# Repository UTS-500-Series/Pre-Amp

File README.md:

# kiCAD Series 500 Compatible Template
Template PCB Series 500 compatible, for kiCAD.
Made by Tormy Van Cool

If this project was useful to you for your porjects and saved you time, please pay me a drink

## Licence

Copyright 2026 the UTS 500 Series team.

This source describes Open Hardware and is licensed under the CERN-OHL-S v2.

You may redistribute and modify this source and make products using it under
the terms of the [CERN-OHL-S v2](https://ohwr.org/cern_ohl_s_v2.txt).

This source is distributed WITHOUT ANY EXPRESS OR IMPLIED WARRANTY, INCLUDING
OF MERCHANTABILITY, SATISFACTORY QUALITY AND FITNESS FOR A PARTICULAR PURPOSE.
Please see the CERN-OHL-S v2 for applicable conditions.

Source location: https://github.com/UTS-500-Series/Pre-Amp

As per CERN-OHL-S v2 section 4, should You produce hardware based on this
source, You must where practicable maintain the Source Location visible on the
external case of the preamp module or other products you make
using this source.

The full licence text is in [LICENSE](LICENSE).

### Third-party material

This licence covers the team's own work. It does not cover, and grants no rights in,
the following:

- **The circuit** is [ESP Project 66](https://sound-au.com/project66.htm) by Rod Elliott,
  with phantom power from [Project 96](https://sound-au.com/project96.htm). ESP's terms
  permit construction for personal use but not commercial manufacture.
- **The board template** (the card outline, edge connector footprint and the text above
  this section) is Tormy Van Cool's kiCAD Series 500 template, published under the GNU GPL
  v3. That material stays under the GPL v3, whose text is kept in
  [LICENSE-GPL-3.0](LICENSE-GPL-3.0).

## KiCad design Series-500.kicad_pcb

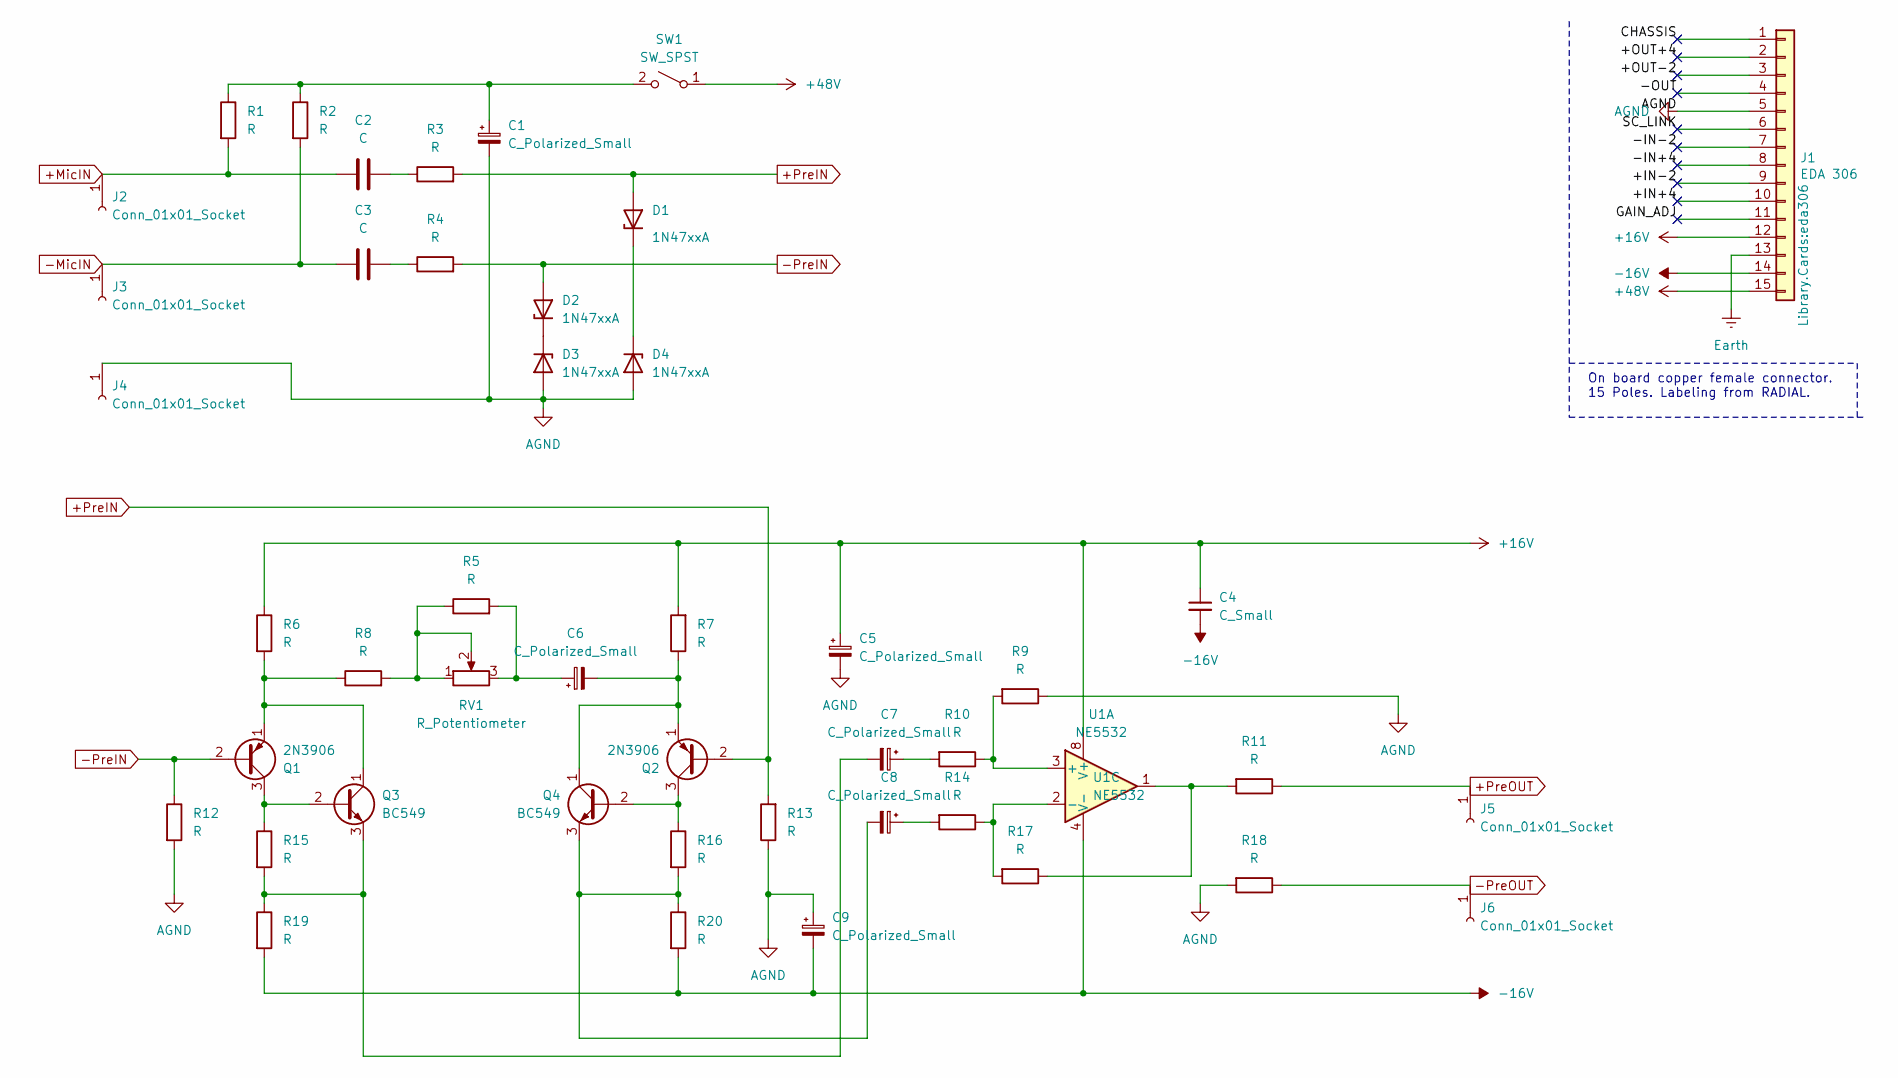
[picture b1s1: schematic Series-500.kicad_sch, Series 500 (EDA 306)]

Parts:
C1: C_Polarized_Small; CP_Radial_D5.0mm_P2.50mm
C2, C3: C; C_Radial_D5.0mm_H5.0mm_P2.00mm
C4: C_Small; C_Disc_D5.0mm_W2.5mm_P5.00mm
C5, C9: C_Polarized_Small; CP_Radial_D8.0mm_P3.80mm
C6: C_Polarized_Small; CP_Radial_D13.0mm_P5.00mm
C7, C8: C_Polarized_Small; CP_Radial_D5.0mm_P2.00mm
D1, D2, D3, D4: 1N47xxA; D_DO-41_SOD81_P10.16mm_Horizontal
J1: EDA 306; eda306
J2, J3, J4, J5, J6: Conn_01x01_Socket; PinHeader_1x01_P2.00mm_Vertical
Q1, Q2: 2N3906; TO-92_Inline
Q3, Q4: BC549; TO-92_Inline
R1, R2, R3, R4, R5, R6, R7, R8, R9, R10, R11, R12, R13, R14, R15, R16, R17, R18, R19, R20: R; R_Axial_DIN0309_L9.0mm_D3.2mm_P12.70mm_Horizontal
RV1: R_Potentiometer; PinHeader_1x03_P2.00mm_Vertical
SW1: SW_SPST; PinHeader_1x02_P2.00mm_Vertical
U1: NE5532; DIP-8_W7.62mm

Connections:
+16V: C4.1, C5.1, J1.12, R6.1, R7.2, U1.8 (V+)
+48V: J1.15, SW1.1 (A)
+MicIN: C2.1, J2.1 (Pin_1_1), R1.2
+PreIN: D1.2 (A), Q2.2 (B), R3.2, R13.2
+PreOUT: J5.1 (Pin_1_1), R11.1
-16V: C4.2, C9.2, J1.14, R19.2, R20.2, U1.4 (V-)
-MicIN: C3.1, J3.1 (Pin_1_1), R2.2
-PreIN: D2.2 (A), Q1.2 (B), R4.2, R12.1
-PreOUT: J6.1 (Pin_1_1), R18.1
/+IN+4: J1.10
/+IN+4_1: J1.10
/+IN-2: J1.9
/+IN-2_1: J1.9
/+OUT+4: J1.2
/+OUT+4_1: J1.2
/+OUT-2: J1.3
/+OUT-2_1: J1.3
/-IN+4: J1.8
/-IN+4_1: J1.8
/-IN-2: J1.7
/-IN-2_1: J1.7
/-OUT: J1.4
/-OUT_1: J1.4
/CHASSIS: J1.1
/CHASSIS_1: J1.1
/GAIN_ADJ: J1.11
/GAIN_ADJ_1: J1.11
/SC_LINK: J1.6
/SC_LINK_1: J1.6
AGND: C1.2, C5.2, C9.1, D3.2 (A), D4.2 (A), J1.5, J4.1 (Pin_1_1), R9.1, R12.2, R13.1, R18.2
Earth: J1.13
unnamed: C2.2, R3.1
unnamed: C3.2, R4.1
unnamed: C6.1, R5.2, RV1.3
unnamed: C7.1, R10.2
unnamed: C8.1, R14.2
unnamed: D1.1 (K), D4.1 (K)
unnamed: D2.1 (K), D3.1 (K)
unnamed: Q1.3 (C), Q3.2 (B), R15.1
unnamed: Q1.1 (E), Q3.1 (C), R6.2, R8.1
unnamed: Q2.3 (C), Q4.2 (B), R16.1
unnamed: C6.2, Q2.1 (E), Q4.1 (C), R7.1
unnamed: C7.2, Q3.3 (E), R15.2, R19.1
unnamed: C8.2, Q4.3 (E), R16.2, R20.1
unnamed: R5.1, R8.2, RV1.1, RV1.2
unnamed: R11.2, R17.1, U1.1
unnamed: C1.1, R1.1, R2.1, SW1.2 (B)
unnamed: R9.2, R10.1, U1.3 (+)
unnamed: R14.1, R17.2, U1.2 (-)

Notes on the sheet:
On board copper female connector. 15 Poles. Labeling from RADIAL.

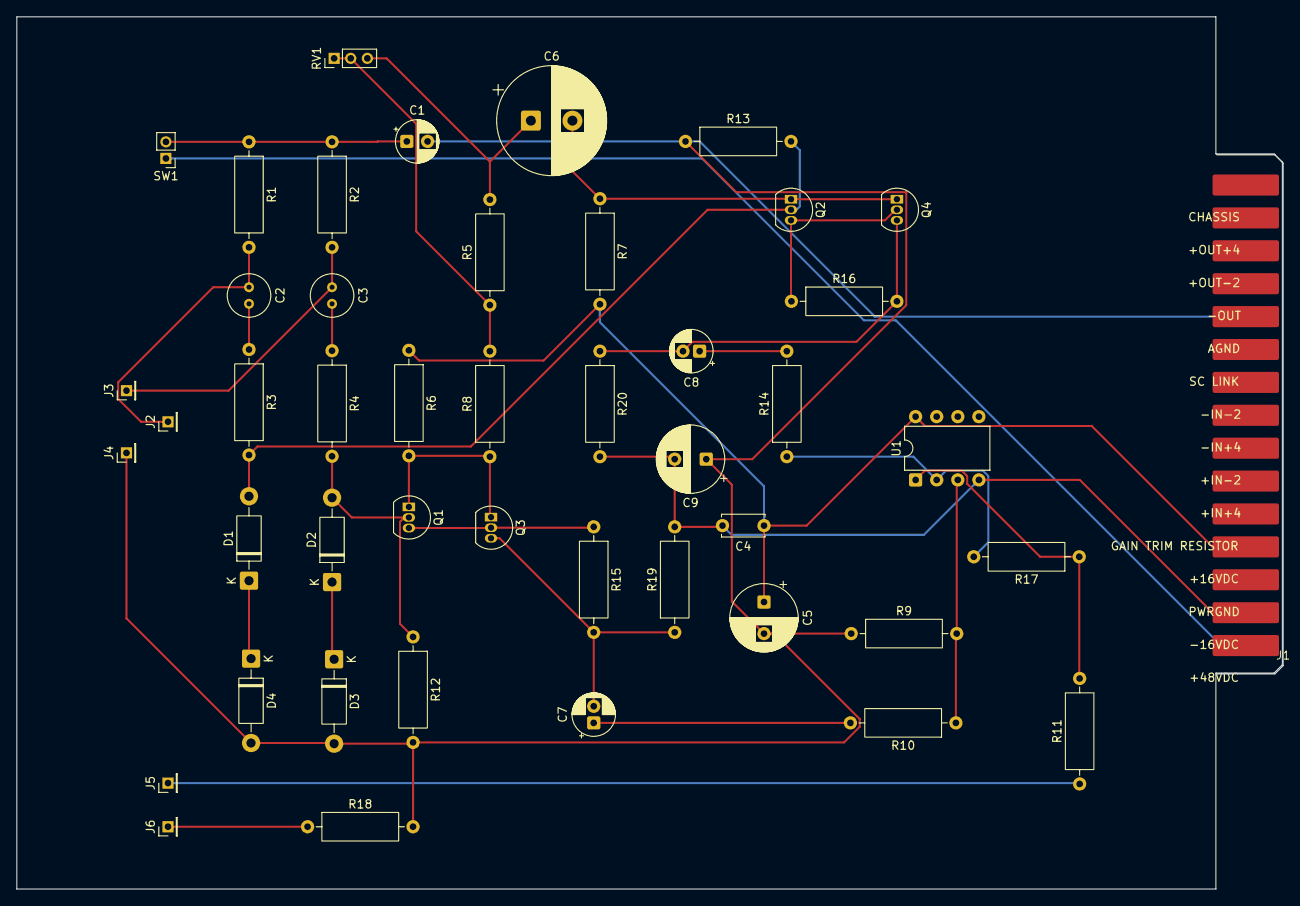
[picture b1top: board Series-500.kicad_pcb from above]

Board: 2 copper layers, 152.3 x 105.0 mm, 46 parts (0 on the bottom side), 28 nets.
